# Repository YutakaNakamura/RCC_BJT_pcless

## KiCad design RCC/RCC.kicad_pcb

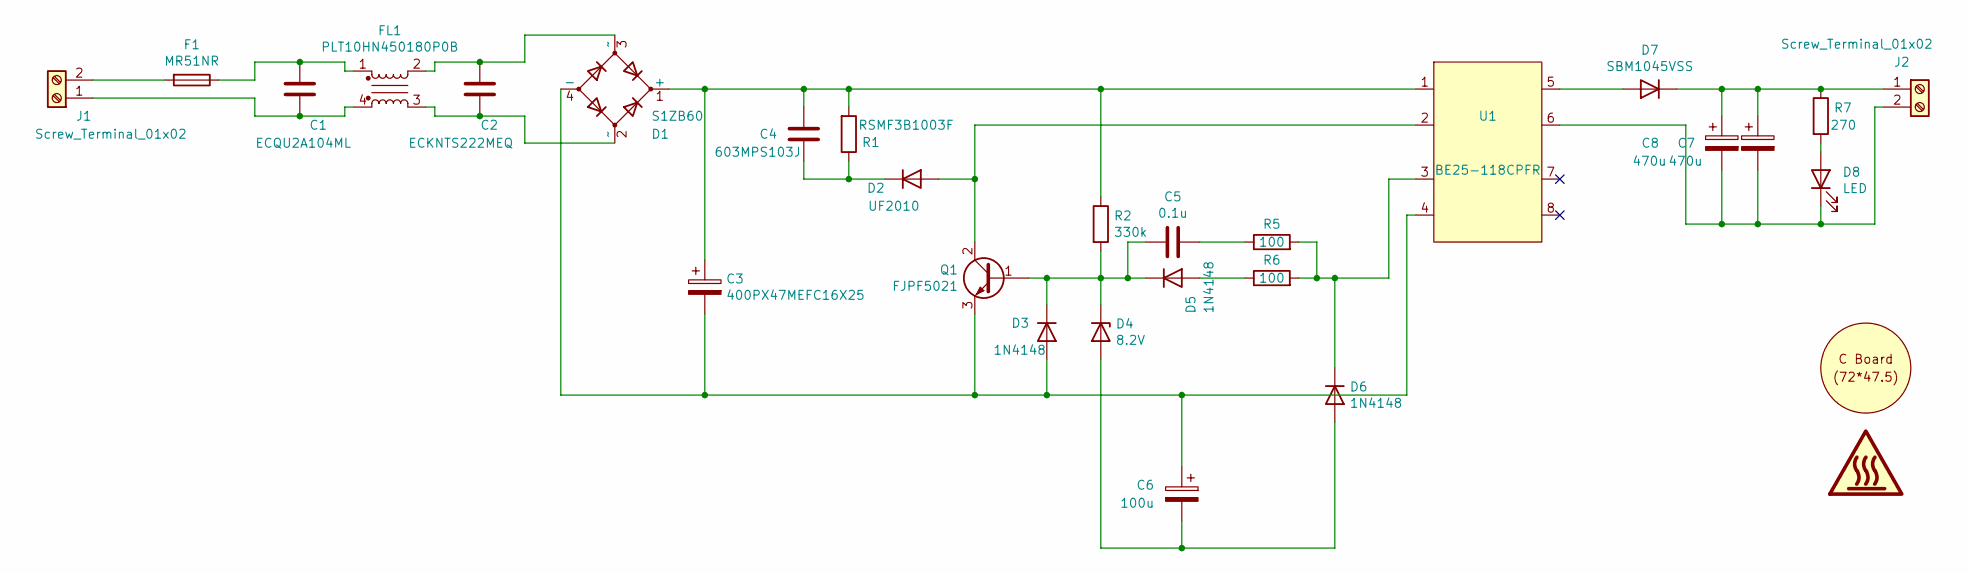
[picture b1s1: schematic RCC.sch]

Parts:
C1: ECQU2A104ML; C_Rect_L18.0mm_W6.0mm_P15.00mm_FKS3_FKP3
C2: ECKNTS222MEQ; C_Disc_D9.0mm_W5.0mm_P7.50mm
C3: 400PX47MEFC16X25; CP_Radial_D16.0mm_P7.50mm
C4: 603MPS103J; C_Rect_L11.5mm_W6.4mm_P10.00mm_MKT
C5: 0.1u; C_Disc_D3.0mm_W1.6mm_P2.50mm
C6: 100u; CP_Radial_D5.0mm_P2.50mm
C7, C8: 470u; CP_Radial_D8.0mm_P3.50mm
D1: S1ZB60
D2: UF2010; D_DO-15_P2.54mm_Vertical_KathodeUp
D3: 1N4148; D_DO-35_SOD27_P5.08mm_Vertical_KathodeUp
D4: 8.2V; D_DO-34_SOD68_P2.54mm_Vertical_KathodeUp
D5, D6: 1N4148; D_DO-35_SOD27_P2.54mm_Vertical_KathodeUp
D7: SBM1045VSS; D_DO-201AE_P5.08mm_Vertical_KathodeUp
D8: LED; D_0603_1608Metric_Pad1.05x0.95mm_HandSolder
F1: MR51NR; Fuseholder_Cylinder-5x20mm_Schurter_0031_8201_Horizontal_Op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
FL1: PLT10HN450180P0B
GUIDE_STAMP1: UniversalBoard_C
J1, J2: Screw_Terminal_01x02; TerminalBlock_bornier-2_P5.08mm
Q1: FJPF5021; TO-220F-3_Vertical
R1: RSMF3B1003F; R_Axial_DIN0614_L14.3mm_D5.7mm_P5.08mm_Vertical
R2: 330k; R_Axial_DIN0207_L6.3mm_D2.5mm_P7.62mm_Horizontal
R5, R6: 100; R_Axial_DIN0207_L6.3mm_D2.5mm_P2.54mm_Vertical
R7: 270; R_0603_1608Metric_Pad0.98x0.95mm_HandSolder
U1: BE25-118CPFR

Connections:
unnamed: C1.1, F1.1, FL1.1
unnamed: C1.2, FL1.4, J1.1
unnamed: C2.1, D1.3 (~~), FL1.2
unnamed: C2.2, D1.2 (~~), FL1.3
unnamed: C3.1, C4.1, D1.1 (+), R1.2, R2.1, U1.1
unnamed: C3.2, C6.1, D1.4 (-), D3.2 (A), Q1.3 (E), U1.4
unnamed: C4.2, D2.1 (K), R1.1
unnamed: C5.1, D3.1 (K), D4.1 (K), D5.1 (K), Q1.1 (B), R2.2
unnamed: C5.2, R5.1
unnamed: C6.2, D4.2 (A), D6.2 (A)
unnamed: C7.1, C8.1, D7.1 (K), J2.1, R7.1
unnamed: C7.2, C8.2, D8.1 (K), J2.2, U1.6
unnamed: D2.2 (A), Q1.2 (C), U1.2
unnamed: D5.2 (A), R6.1
unnamed: D6.1 (K), R5.2, R6.2, U1.3
unnamed: D7.2 (A), U1.5
unnamed: D8.2 (A), R7.2
unnamed: F1.2, J1.2

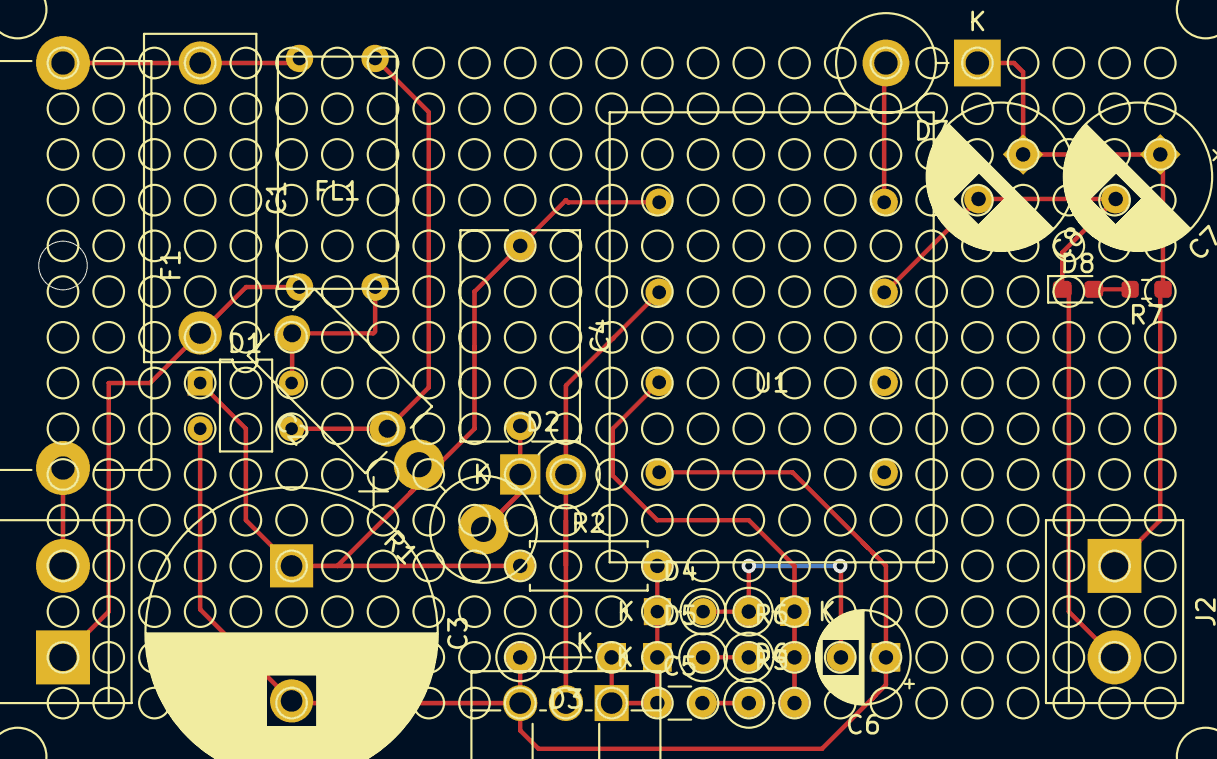
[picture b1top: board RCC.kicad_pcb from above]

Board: 2 copper layers, 28 parts (0 on the bottom side), 18 nets.

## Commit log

2021-03-16 [add] KiCAD/LTSpiceを追加
